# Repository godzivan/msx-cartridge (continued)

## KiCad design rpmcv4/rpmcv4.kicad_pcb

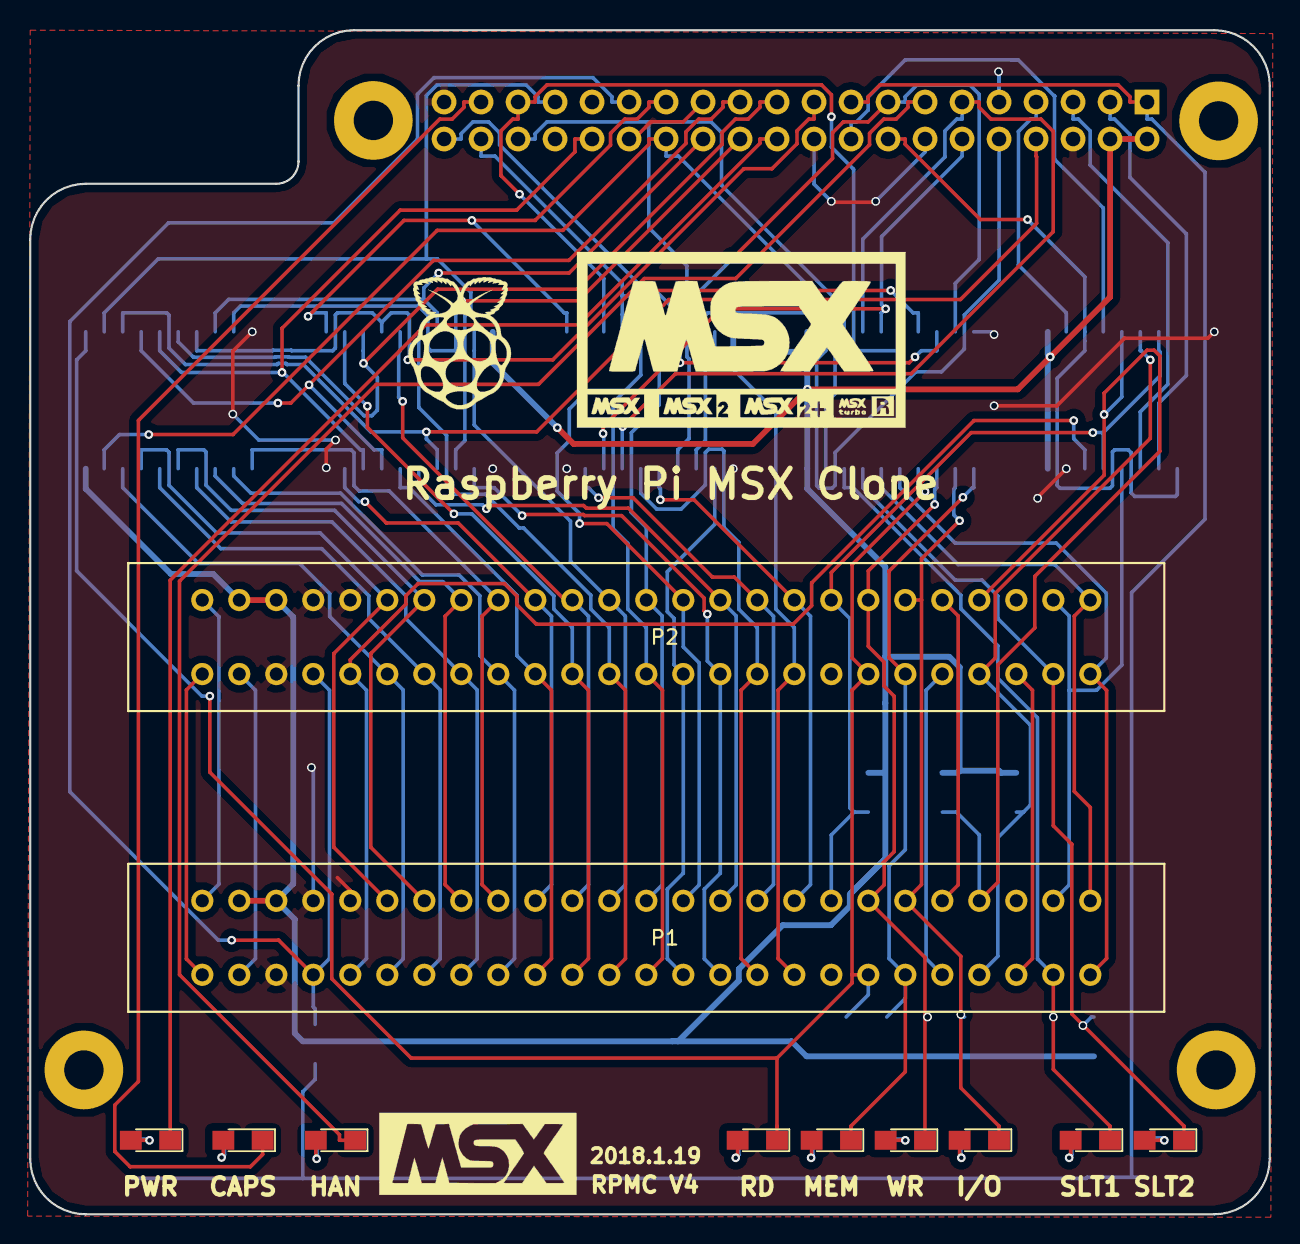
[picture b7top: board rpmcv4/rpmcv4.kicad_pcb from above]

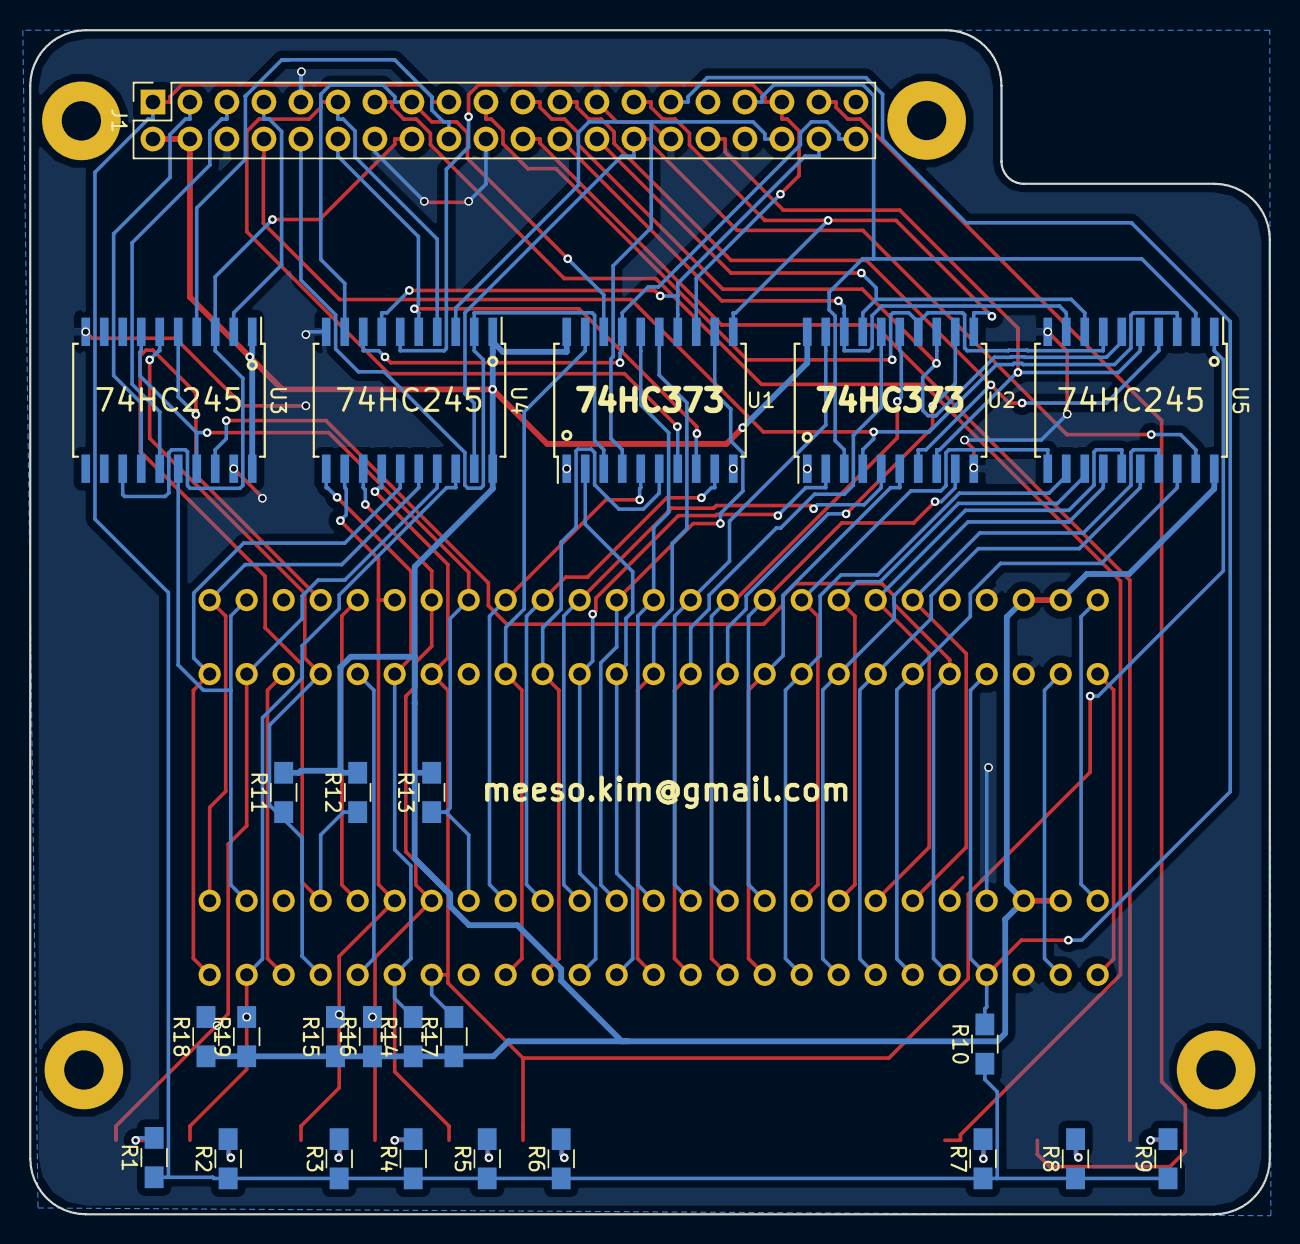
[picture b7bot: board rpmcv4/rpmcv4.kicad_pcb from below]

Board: 2 copper layers, 85.1 x 81.3 mm, 40 parts (25 on the bottom side), 82 nets.

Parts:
D1, D2, D3, D4, D5, D6, D7, D8, D9: Led_Small; LED_0805_HandSoldering
J1: RPi_GPIO; Socket_Strip_Straight_2x20_Pitch2.54mm
P1, P2: CONN_02X25; MSX_SLOT
R1, R2, R3, R4, R5, R6, R7, R8, R9, R10, R11, R12, R13, R14, R15, R16, R17, R18, R19: R; R_0805_HandSoldering
REF1, REF2, REF3, REF4: MountingHole_2.7mm_Pad
U1, U2: 74LS373; SOIC-20W_7.5x12.8mm_Pitch1.27mm
U3, U4, U5: 74LS245; SOIC-20W_7.5x12.8mm_Pitch1.27mm

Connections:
+3V3: J1.1, J1.17, R1.1, R2.1, R3.1, R4.1, R5.1, R6.1, R7.1, R8.1, R9.1, R10.1
+5V: J1.2, J1.4, P1.45, P1.47, P2.45, P2.47, R11.2, R12.2, R13.1, R14.1, R15.1, R16.1, R17.1, R18.1, R19.1, U1.20, U2.20, U3.1, U3.20, U4.1, U4.20, U5.20
/+12V: P1.48, P2.48
/+V12: P1.50, P2.50
/A0: P1.28, P2.28, U2.16
/A1: P1.27, P2.27, U2.19
/A2: P1.30, P2.30, U2.12
/A3: P1.29, P2.29, U2.15
/A4: P1.32, P2.32, U2.6
/A5: P1.31, P2.31, U2.9
/A6: P1.22, P2.22, U2.2
/A7: P1.21, P2.21, U2.5
/A8: P1.24, P2.24, U1.2
/A9: P1.17, P2.17, U1.5
/A10: P1.20, P2.20, U1.6
/A11: P1.19, P2.19, U1.9
/A12: P1.23, P2.23, U1.12
/A13: P1.26, P2.26, U1.15
/A14: P1.25, P2.25, U1.16
/A15: P1.18, P2.18, U1.19
/BUSDIR: P1.10, P2.10
/CAPS: D8.1, J1.37
/CLK: P1.42, P2.42, U3.18
/CS1: P1.1, P2.1, U4.16
/CS2: P1.2, P2.2, U4.15
/CS12: P1.3, P2.3, U3.16
/D0: P1.34, P2.34, U5.12
/D1: P1.33, P2.33, U5.11
/D2: P1.36, P2.36, U5.14
/D3: P1.35, P2.35, U5.13
/D4: P1.38, P2.38, U5.16
/D5: P1.37, P2.37, U5.15
/D6: P1.40, P2.40, U5.18
/D7: P1.39, P2.39, U5.17
/HAN: D7.1, J1.13
/INT: P1.8, P2.8, R11.1, U3.6
/IORQ: D3.1, P1.11, P2.11, R15.2, U4.12
/LE_A: J1.27, U1.11, U2.11
/LE_B: J1.28, U4.19, U5.19
/M1: P1.9, P2.9
/MREQ: D5.1, P1.12, P2.12, R14.2, U4.11
/PWR: D9.1, J1.22
/RA8: J1.10, U1.3, U4.2
/RA9: J1.36, U1.4, U4.3
/RA10: J1.11, U1.7, U4.4
/RA11: J1.12, U1.8, U4.5
/RA12: J1.35, U1.13, U4.6
/RA13: J1.38, U1.14, U4.7
/RA14: J1.40, U1.17, U4.8
/RA15: J1.15, U1.18, U4.9
/RCLK: J1.7, U3.2
/RCS12: J1.18, U3.4
/RD: D6.1, P1.14, P2.14, R17.2, U4.14, U5.1
/RD0: J1.26, U2.17, U5.8
/RD1: J1.24, U2.18, U5.9
/RD2: J1.21, U2.13, U5.6
/RD3: J1.19, U2.14, U5.7
/RD4: J1.23, U2.7, U5.4
/RD5: J1.32, U2.8, U5.5
/RD6: J1.33, U2.3, U5.2
/RD7: J1.8, U2.4, U5.3
/RESET: P1.15, P2.15, R13.2, U3.7, U3.17
/RFSH: P1.6, P2.6
/RINT: J1.3, U3.14
/RRESET: J1.16, U3.3, U3.13
/RWAIT: J1.5, U3.15
/SLTSL1: D2.1, P1.4, R19.2, U4.18
/SLTSL3: D1.1, P2.4, R18.2, U4.17
/SNDIN: P1.49, P2.49
/SW1: J1.29, P1.44, P2.44, R10.2
/WAIT: P1.7, P2.7, R12.1, U3.5
/WR: D4.1, P1.13, P2.13, R16.2, U4.13
GND: J1.6, J1.9, J1.14, J1.20, J1.25, J1.30, J1.34, J1.39, P1.41, P1.43, P1.46, P2.41, P2.43, P2.46, U1.1, U1.10, U2.1, U2.10, U3.10, U3.19, U4.10, U5.10
unnamed: D1.2, R1.2
unnamed: D2.2, R2.2
unnamed: D3.2, R3.2
unnamed: D4.2, R4.2
unnamed: D5.2, R5.2
unnamed: D6.2, R6.2
unnamed: D7.2, R7.2
unnamed: D8.2, R8.2
unnamed: D9.2, R9.2
